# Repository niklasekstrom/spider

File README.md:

# SPIder

## Introduction

SPIder is an adapter that connects to the clockport on an Amiga, and provides
two SPI controllers and additional GPIO pins.

SPIder is built around the RP2040 microcontroller. GPIO pins 0..15 on the RP2040
are connected to the clockport, and pins 16..29 are available on a pin header.
GPIO pins 16..29 have multiple alternative functions. A table with the possible
functions for the GPIO pins are available in
[section 1.4.3](https://datasheets.raspberrypi.com/rp2040/rp2040-datasheet.pdf#page=13)
of the RP2040 datasheet.

## Architecture

This section contains a high level overview of the architecture of the firmware.
The RP2040 has two Cortex-M0+ ARM cores. One core is dedicated to responding to
clockport accesses (reads and writes). This has to be done in a time sensitive
manner as a clockport access lasts for less than a microsecond. The other core
communicates with the peripherals on the RP2040, such as the two SPI
controllers.

## Bill of Materials (BOM)

| References | Value | Footprint | Quantity | JLCPCB |
|------------|-------|-----------|----------|--------|
| C5, C6, C7, C9, C11, C12, C13, C14, C15, C16, C18, C19, C20 | 100n | C_0402_1005Metric | 13 | [C1525](https://jlcpcb.com/partdetail/1877-CL05B104KO5NNNC/C1525) |
| C1, C4 | 10u | C_0805_2012Metric | 2 | [C15850](https://jlcpcb.com/partdetail/16532-CL21A106KAYNNNE/C15850) |
| C2, C3 | 15p | C_0402_1005Metric | 2 | [C1548](https://jlcpcb.com/partdetail/1900-0402CG150J500NT/C1548) |
| C8, C10 | 1u | C_0402_1005Metric | 2 | [C52923](https://jlcpcb.com/partdetail/53938-CL05A105KA5NQNC/C52923) |
| R2, R3 | 27 | R_0402_1005Metric | 2 | [C25105](https://jlcpcb.com/partdetail/25848-0402WGF330JTCE/C25105) |
| R1 | 10k | R_0402_1005Metric | 1 | [C25744](https://jlcpcb.com/partdetail/26487-0402WGF1002TCE/C25744) |
| R5 | 1k | R_0402_1005Metric | 1 | [C11702](https://jlcpcb.com/partdetail/12256-0402WGF1001TCE/C11702) |
| U1 | RP2040 | QFN-56-1EP_7x7mm_P0.4mm_EP3.2x3.2mm | 1 | [C2040](https://jlcpcb.com/partdetail/RaspberryPi-RP2040/C2040) |
| Y1 | ABM8-272-T3 | Crystal_SMD_3225-4Pin_3.2x2.5mm | 1 | [C20625731](https://jlcpcb.com/partdetail/AbraconLlc-ABM8_272T3/C20625731) |
| IC1 | SN74CBTD3384CPWR | TSSOP-24_4.4x7.8mm_P0.65mm | 1 | [C484747](https://jlcpcb.com/partdetail/TexasInstruments-SN74CBTD3384CPWR/C484747) |
| IC2 | SN74LVC125AIPWREP | TSSOP-14_4.4x5mm_P0.65mm | 1 | [C7813](https://jlcpcb.com/partdetail/TexasInstruments-SN74LVC125APWR/C7813) |
| IC3 | SN74LVC2G32DCUR | VSSOP-8_2.3x2mm_P0.5mm | 1 | [C91874](https://jlcpcb.com/partdetail/TexasInstruments-SN74LVC2G32DCUR/C91874) |
| IC4 | W25Q32RVXHJQ_TR | Winbond_USON-8-1EP_3x2mm_P0.5mm_EP0.2x1.6mm | 1 | [C5258281](https://jlcpcb.com/partdetail/Zetta-ZD25WQ32CEIGR/C5258281) |
| IC5 | TLV1117LV33DCYR | SOT-223 | 1 | [C15578](https://jlcpcb.com/partdetail/TexasInstruments-TLV1117LV33DCYR/C15578) |
| J1 | Conn_02x11_Odd_Even | PinSocket_2x11_P2.00mm_Vertical | 1 | |
| J2 | Conn_02x10_Odd_Even | PinHeader_2x10_P2.54mm_Horizontal | 1 | |
| J3 | Conn_01x03 | PinHeader_1x03_P2.54mm_Vertical | 1 | |
| J4 | Conn_01x05 | PinHeader_1x05_P2.54mm_Vertical | 1 | |

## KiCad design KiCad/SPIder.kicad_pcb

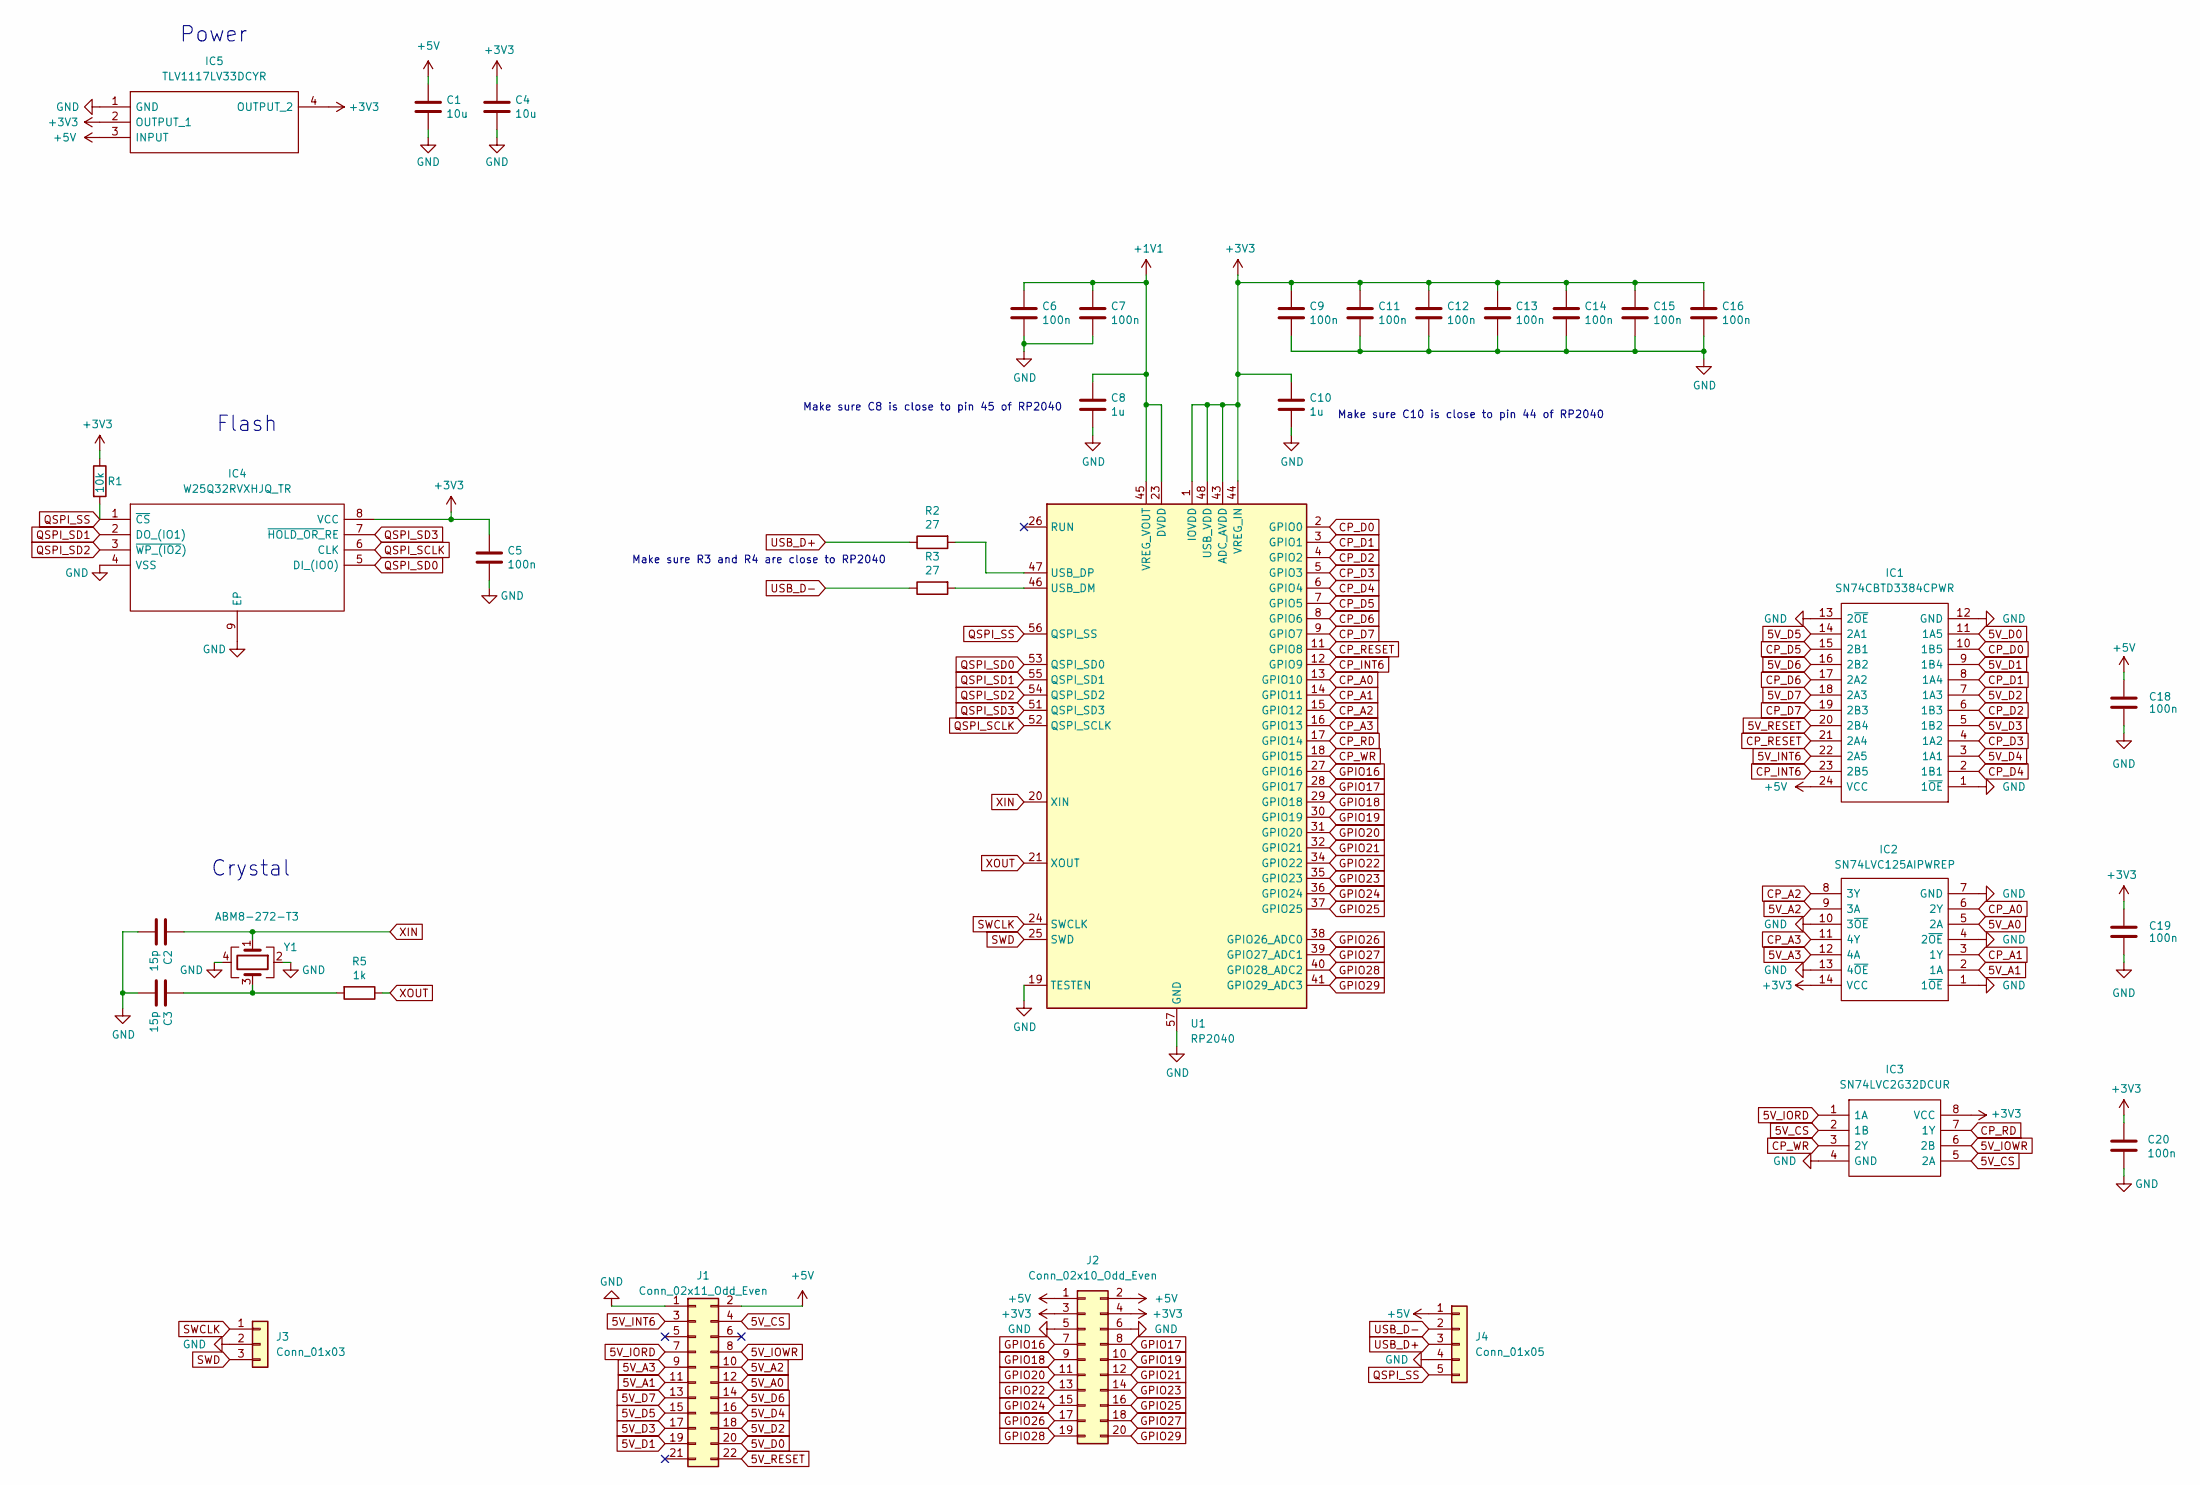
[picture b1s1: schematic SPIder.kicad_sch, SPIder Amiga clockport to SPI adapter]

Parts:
C1, C4: 10u; C_0805_2012Metric
C2, C3: 15p; C_0402_1005Metric
C5, C6, C7, C9, C11, C12, C13, C14, C15, C16, C18, C19, C20: 100n; C_0402_1005Metric
C8, C10: 1u; C_0402_1005Metric
IC1: SN74CBTD3384CPWR; TSSOP-24_4.4x7.8mm_P0.65mm; Mouser Part Number 595-SN74CBTD3384CPWR
IC2: SN74LVC125AIPWREP; TSSOP-14_4.4x5mm_P0.65mm; Mouser Part Number 595-N74LVC125AIPWREP
IC3: SN74LVC2G32DCUR; VSSOP-8_2.3x2mm_P0.5mm; Mouser Part Number 595-SN74LVC2G32DCUR
IC4: W25Q32RVXHJQ_TR; Winbond_USON-8-1EP_3x2mm_P0.5mm_EP0.2x1.6mm; Mouser Part Number 454-W25Q32RVXHJQTR
IC5: TLV1117LV33DCYR; SOT-223; Mouser Part Number 595-TLV1117LV33DCYR
J1: Conn_02x11_Odd_Even; PinSocket_2x11_P2.00mm_Vertical
J2: Conn_02x10_Odd_Even; PinHeader_2x10_P2.54mm_Horizontal
J3: Conn_01x03; PinHeader_1x03_P2.54mm_Vertical
J4: Conn_01x05; PinHeader_1x05_P2.54mm_Vertical
R1: 10k; R_0402_1005Metric
R2, R3: 27; R_0402_1005Metric
R5: 1k; R_0402_1005Metric
U1: RP2040; QFN-56-1EP_7x7mm_P0.4mm_EP3.2x3.2mm
Y1: ABM8-272-T3; Crystal_SMD_3225-4Pin_3.2x2.5mm

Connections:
5V_A0: IC2.5 (2A), J1.12
5V_A1: IC2.2 (1A), J1.11
5V_A2: IC2.9 (3A), J1.10
5V_A3: IC2.12 (4A), J1.9
5V_CS: IC3.2 (1B), IC3.5 (2A), J1.4
5V_D0: IC1.11 (1A5), J1.20
5V_D1: IC1.9 (1B4), J1.19
5V_D2: IC1.7 (1A3), J1.18
5V_D3: IC1.5 (1B2), J1.17
5V_D4: IC1.3 (1A1), J1.16
5V_D5: IC1.14 (2A1), J1.15
5V_D6: IC1.16 (2B2), J1.14
5V_D7: IC1.18 (2A3), J1.13
5V_INT6: IC1.22 (2A5), J1.3
5V_IORD: IC3.1 (1A), J1.7
5V_IOWR: IC3.6 (2B), J1.8
5V_RESET: IC1.20 (2B4), J1.22
+1V1: C6.1, C7.1, C8.1, U1.23 (DVDD), U1.45 (VREG_VOUT), U1.50 (DVDD)
+3V3: C4.1, C5.1, C9.1, C10.1, C11.1, C12.1, C13.1, C14.1, C15.1, C16.1, C19.1, C20.1, IC2.14 (VCC), IC3.8 (VCC), IC4.8 (VCC), IC5.2 (OUTPUT_1), IC5.4 (OUTPUT_2), J2.3, J2.4, R1.1, U1.1 (IOVDD), U1.10 (IOVDD), U1.22 (IOVDD), U1.33 (IOVDD), U1.42 (IOVDD), U1.43 (ADC_AVDD), U1.44 (VREG_IN), U1.48 (USB_VDD), U1.49 (IOVDD)
+5V: C1.1, C18.1, IC1.24 (VCC), IC5.3 (INPUT), J1.2, J2.1, J2.2, J4.1
CP_A0: IC2.6 (2Y), U1.13 (GPIO10)
CP_A1: IC2.3 (1Y), U1.14 (GPIO11)
CP_A2: IC2.8 (3Y), U1.15 (GPIO12)
CP_A3: IC2.11 (4Y), U1.16 (GPIO13)
CP_D0: IC1.10 (1B5), U1.2 (GPIO0)
CP_D1: IC1.8 (1A4), U1.3 (GPIO1)
CP_D2: IC1.6 (1B3), U1.4 (GPIO2)
CP_D3: IC1.4 (1A2), U1.5 (GPIO3)
CP_D4: IC1.2 (1B1), U1.6 (GPIO4)
CP_D5: IC1.15 (2B1), U1.7 (GPIO5)
CP_D6: IC1.17 (2A2), U1.8 (GPIO6)
CP_D7: IC1.19 (2B3), U1.9 (GPIO7)
CP_INT6: IC1.23 (2B5), U1.12 (GPIO9)
CP_RD: IC3.7 (1Y), U1.17 (GPIO14)
CP_RESET: IC1.21 (2A4), U1.11 (GPIO8)
CP_WR: IC3.3 (2Y), U1.18 (GPIO15)
GND: C1.2, C2.2, C3.2, C4.2, C5.2, C6.2, C7.2, C8.2, C9.2, C10.2, C11.2, C12.2, C13.2, C14.2, C15.2, C16.2, C18.2, C19.2, C20.2, IC1.1 (1~OE), IC1.12 (GND), IC1.13 (2~OE), IC2.1 (1~OE), IC2.4 (2~OE), IC2.7 (GND), IC2.10 (3~OE), IC2.13 (4~OE), IC3.4 (GND), IC4.4 (VSS), IC4.9 (EP), IC5.1 (GND), J1.1, J2.5, J2.6, J3.2, J4.4, U1.19 (TESTEN), U1.57 (GND), Y1.2, Y1.4
GPIO16: J2.7, U1.27 (GPIO16)
GPIO17: J2.8, U1.28 (GPIO17)
GPIO18: J2.9, U1.29 (GPIO18)
GPIO19: J2.10, U1.30 (GPIO19)
GPIO20: J2.11, U1.31 (GPIO20)
GPIO21: J2.12, U1.32 (GPIO21)
GPIO22: J2.13, U1.34 (GPIO22)
GPIO23: J2.14, U1.35 (GPIO23)
GPIO24: J2.15, U1.36 (GPIO24)
GPIO25: J2.16, U1.37 (GPIO25)
GPIO26: J2.17, U1.38 (GPIO26_ADC0)
GPIO27: J2.18, U1.39 (GPIO27_ADC1)
GPIO28: J2.19, U1.40 (GPIO28_ADC2)
GPIO29: J2.20, U1.41 (GPIO29_ADC3)
unnamed: C3.1, R5.2, Y1.3
unnamed: R3.2, U1.46 (USB_DM)
unnamed: R2.2, U1.47 (USB_DP)
QSPI_SCLK: IC4.6 (CLK), U1.52 (QSPI_SCLK)
QSPI_SD0: IC4.5 (DI_(IO0)), U1.53 (QSPI_SD0)
QSPI_SD1: IC4.2 (DO_(IO1)), U1.55 (QSPI_SD1)
QSPI_SD2: IC4.3 (~WP_(IO2)), U1.54 (QSPI_SD2)
QSPI_SD3: IC4.7 (~HOLD_OR_RE), U1.51 (QSPI_SD3)
QSPI_SS: IC4.1 (~CS), J4.5, R1.2, U1.56 (QSPI_SS)
SWCLK: J3.1, U1.24 (SWCLK)
SWD: J3.3, U1.25 (SWD)
USB_D+: J4.3, R2.1
USB_D-: J4.2, R3.1
XIN: C2.1, U1.20 (XIN), Y1.1
XOUT: R5.1, U1.21 (XOUT)

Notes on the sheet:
Power
Crystal
Make sure C8 is close to pin 45 of RP2040
Make sure R3 and R4 are close to RP2040
Make sure C10 is close to pin 44 of RP2040
Flash

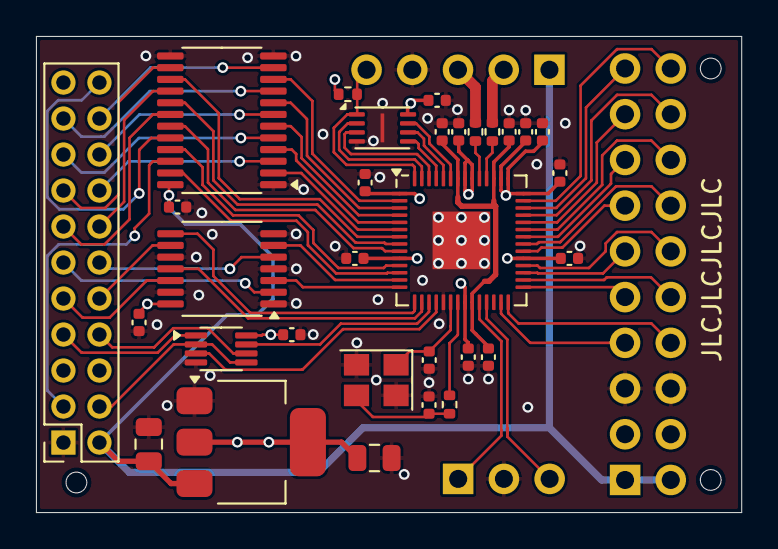
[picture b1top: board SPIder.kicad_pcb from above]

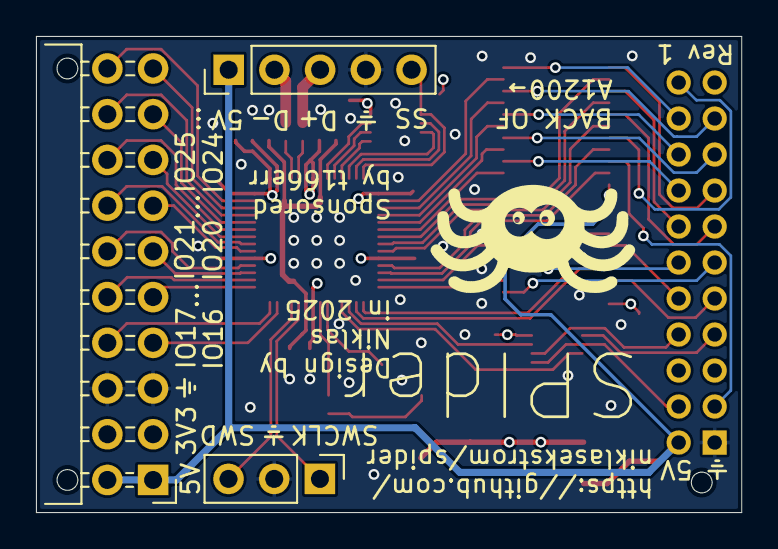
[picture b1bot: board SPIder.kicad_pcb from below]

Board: 4 copper layers, 39.2 x 26.5 mm, 34 parts (3 on the bottom side), 66 nets.

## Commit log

2025-05-18 Initial commit, revision 1
2025-05-18 Add SPIder logo as png image
2025-05-23 Update README with more text and BOM
